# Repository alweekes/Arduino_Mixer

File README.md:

This is an Arduino Nano based hardware mixer control for use with deej project (https://github.com/omriharel/deej).

The idea is based on the Snackboard mix here (https://github.com/Snackya/Snackboard-mix).

I liked the idea of using a PCB as a clearly printed front panel, but used different slide potentiometers and decided to buy cheap knobs, rather than print them.

As I also have a 3D printer the final design will include a 3D printed spacer to act as a case, sandwiched between the two PCB's used for the project.

One PCB is unpopulated and will be used as a front panel, the other will be populated and carry the components. I've used a ground plane on the front face and a power plane on the rear to carry the 0V/5V signals to the pots, whilst 
the wipers are routed to the relevant Arduino ADC inputs.

A full BOM and 3D models of the pot's will be available in the project, once completed.

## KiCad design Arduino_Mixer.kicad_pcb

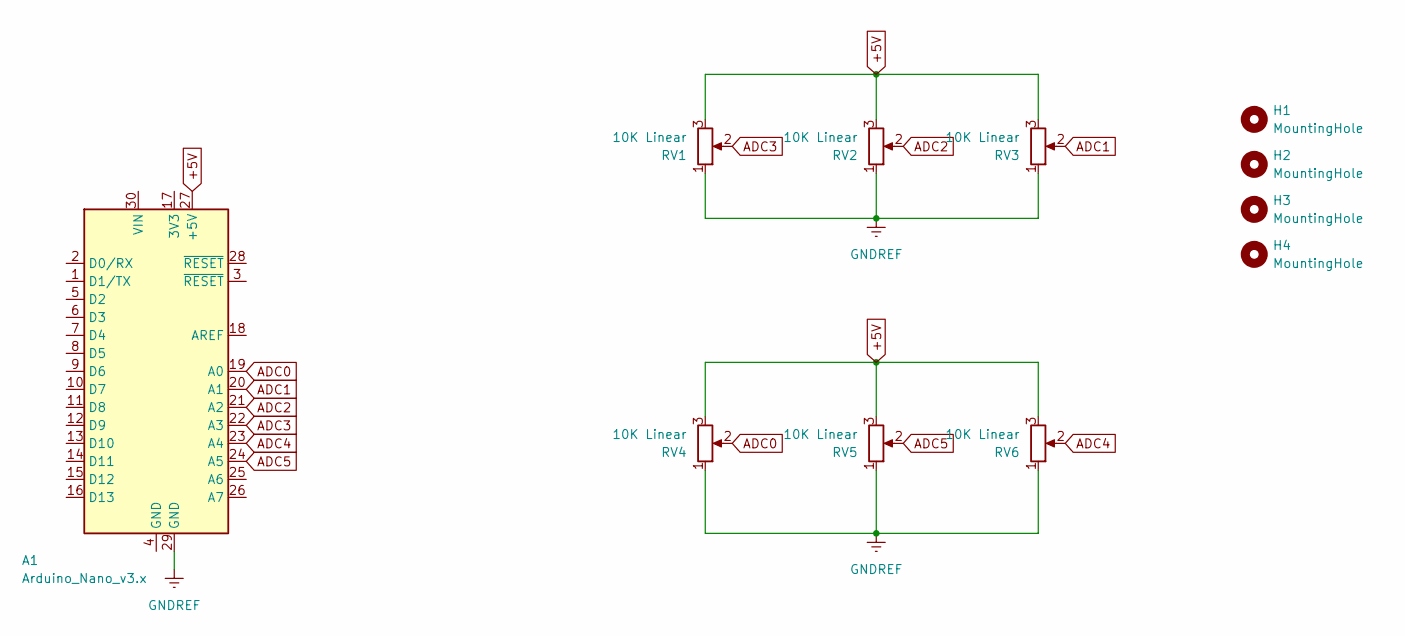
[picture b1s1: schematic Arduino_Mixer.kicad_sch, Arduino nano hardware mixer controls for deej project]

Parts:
A1: Arduino_Nano_v3.x; Arduino_Nano
H1, H2, H3, H4: MountingHole; MountingHole_3.2mm_M3_ISO14580
RV1, RV2, RV3, RV4, RV5, RV6: 10K Linear; Potentiometer_Slide_60mm_Switch_Electronics

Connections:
+5V: A1.27 (+5V), RV1.3, RV2.3, RV3.3, RV4.3, RV5.3, RV6.3
ADC0: A1.19 (A0), RV4.2
ADC1: A1.20 (A1), RV3.2
ADC2: A1.21 (A2), RV2.2
ADC3: A1.22 (A3), RV1.2
ADC4: A1.23 (A4), RV6.2
ADC5: A1.24 (A5), RV5.2
GNDREF: A1.29 (GND), RV1.1, RV2.1, RV3.1, RV4.1, RV5.1, RV6.1

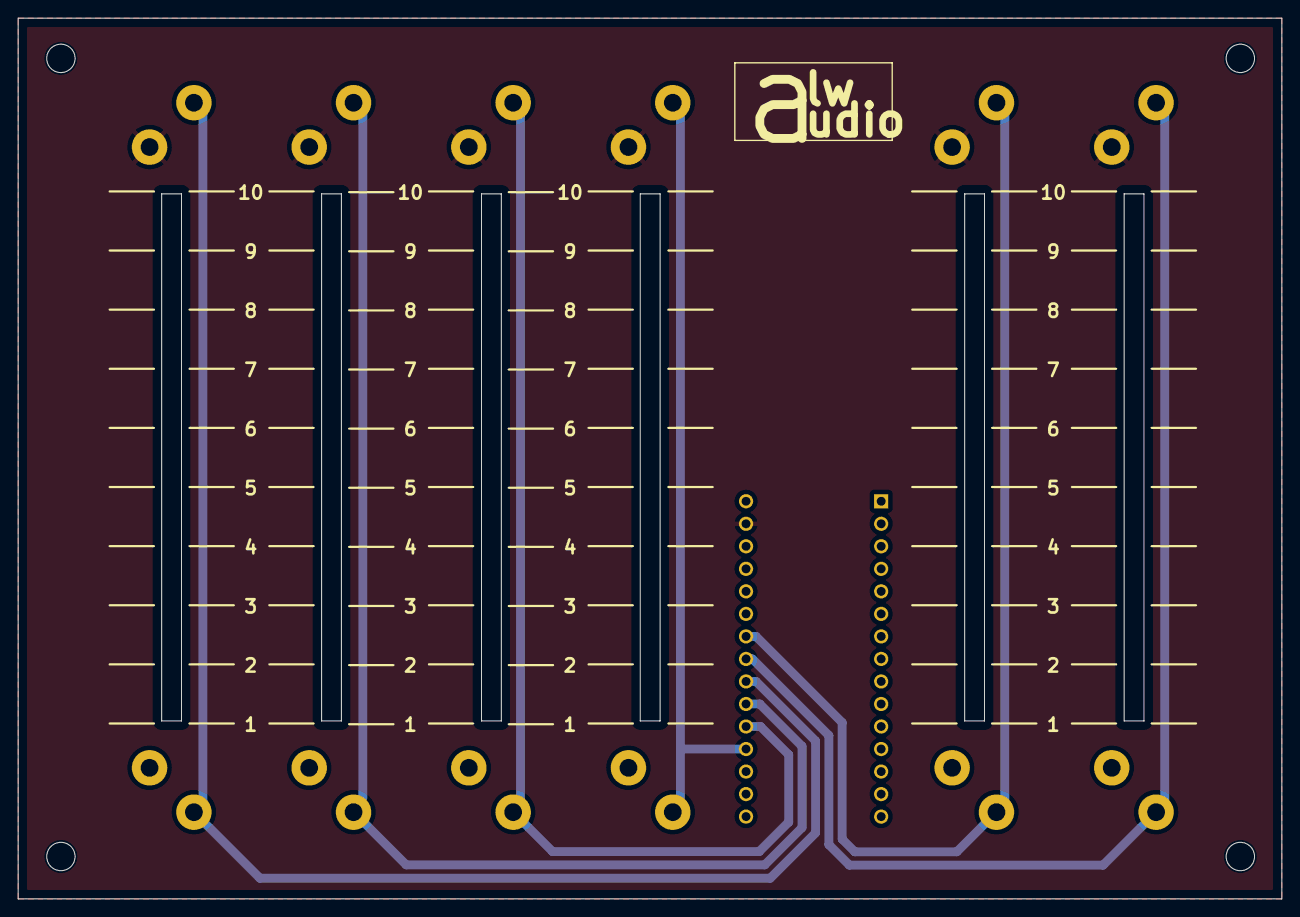
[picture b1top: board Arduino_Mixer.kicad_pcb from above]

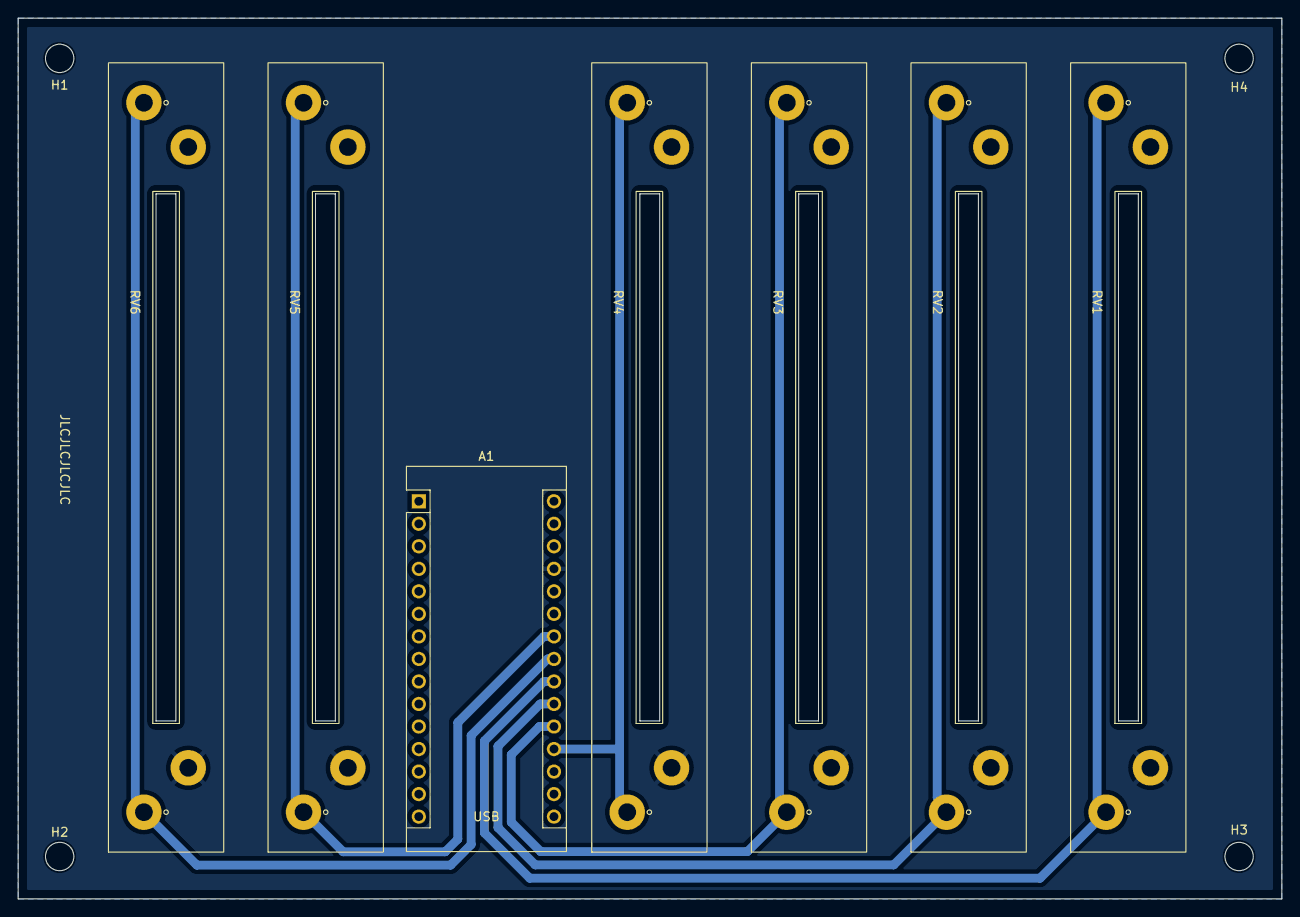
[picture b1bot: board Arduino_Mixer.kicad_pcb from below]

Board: 2 copper layers, 142.5 x 99.3 mm, 11 parts (11 on the bottom side), 8 nets.

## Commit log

2024-03-29 Update to latest version prior to version control implementation
2024-03-30 Added Arduino Nano 3D model.
2024-03-30 Added 3D Model for 60mm Slide Ppotentiometer
2024-03-30 Added initial README file
2024-03-30 Updated README formatting.
2024-03-30 Added Potentiometer 3D model
2024-03-30 Added 4 corner and 1 mid mounting hole for PCB. Generated 3D model output to use when creating 3D printed spacer (using Freecad and KiCadStepUp plugin)
2024-03-30 Tidied project folder
2024-03-30 Removed central hole as assymetry would not have worked with assembled PCB when flipped
2024-03-30 Added files for transfer to OnShape for 3D print design.
2024-03-31 First release candidate Added alw Audio logo, produced gerber plots using JLPCB guidelines: https://jlcpcb.com/help/article/362-how-to-generate-gerber-and-drill-files-in-kicad-8
2024-03-31 Run DRC, regenerate Gerbers and relocate to plot folder.
2024-03-31 Added JLPCB order number location in bottom silk.
2024-03-31 Moved corner hole idents to bottom silk.
2024-03-31 Added final design images.
2024-03-31 Added Bill of Materials
2024-03-31 Added 3D Print files
2024-04-08 Added deej Arduino modified code for 6 sliders
    First PCB release slightly restricts the full movement of the slide potentiometers, so the full 0-1023 output range is not achieved.
    Since there is plenty of resolution added a map and constrain function to scale the analog read values to produce the full 0-1023 output values.
    Changed order of analog inputs so sliders in config.yaml appear in the correct order.
